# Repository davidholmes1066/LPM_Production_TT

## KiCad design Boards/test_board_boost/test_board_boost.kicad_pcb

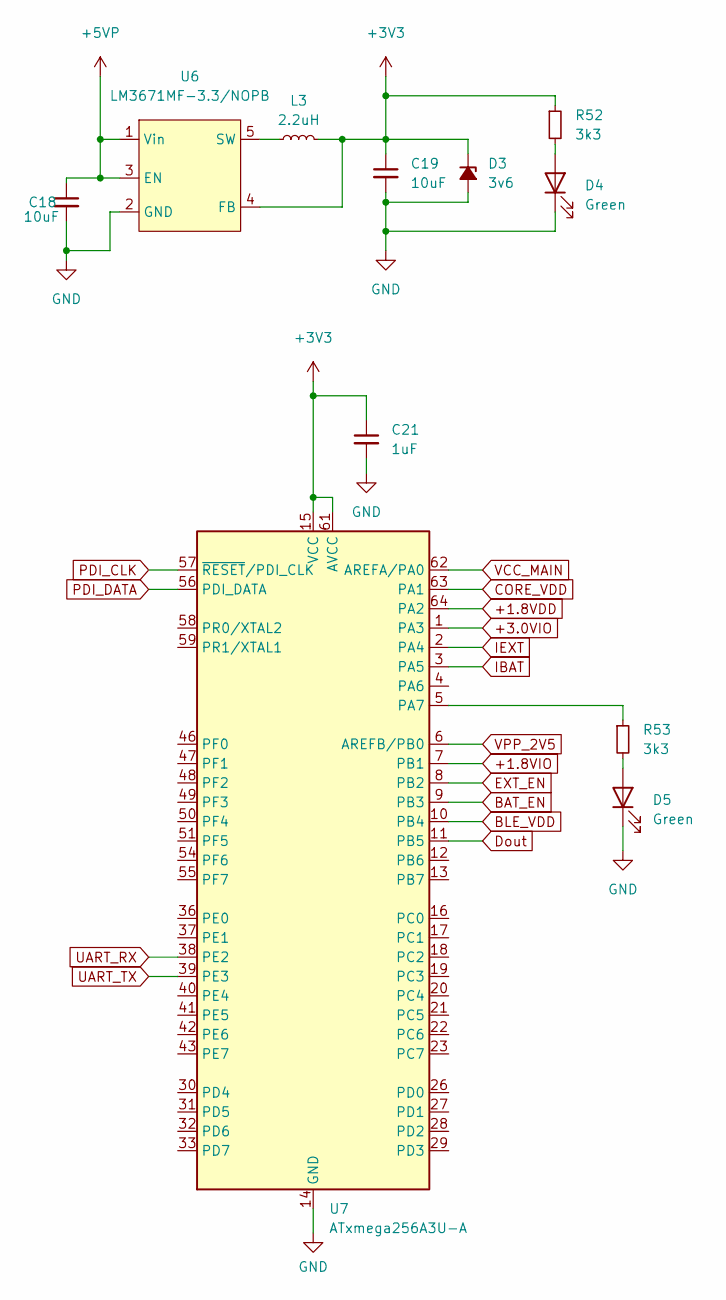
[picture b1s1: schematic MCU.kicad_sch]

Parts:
C18, C19: 10uF; C_0805_2012Metric_Pad1.18x1.45mm_HandSolder
C21: 1uF; C_0805_2012Metric_Pad1.18x1.45mm_HandSolder; Farnell 2346944
D3: 3v6; BZX84C3V6; Farnell 1902466
D4, D5: Green; LED_0402_1005Metric_Pad0.77x0.64mm_HandSolder; Farnell 2507544
L3: 2.2uH; 10uH_boost; Farnell 3865051
R52, R53: 3k3; R_0805_2012Metric_Pad1.20x1.40mm_HandSolder
U6: LM3671MF-3.3/NOPB; SOT-23-5_HandSoldering; Farnell 3008192
U7: ATxmega256A3U-A; TQFP-64_14x14mm_P0.8mm

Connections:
+1.8VDD: U7.64 (PA2); also elsewhere on the board
+1.8VIO: U7.7 (PB1); also elsewhere on the board
+3.0VIO: U7.1 (PA3); also elsewhere on the board
+3V3: C19.1, C21.1, D3.1 (K), L3.2, R52.1, U6.4 (FB), U7.15 (VCC), U7.25 (VCC), U7.35 (VCC), U7.45 (VCC), U7.53 (VCC), U7.61 (AVCC); also elsewhere on the board
+5VP: C18.1, U6.1 (Vin), U6.3 (EN); also elsewhere on the board
BAT_EN: U7.9 (PB3); also elsewhere on the board
BLE_VDD: U7.10 (PB4); also elsewhere on the board
CORE_VDD: U7.63 (PA1); also elsewhere on the board
Dout: U7.11 (PB5); also elsewhere on the board
EXT_EN: U7.8 (PB2); also elsewhere on the board
GND: C18.2, C19.2, C21.2, D3.2 (A), D4.1 (K), D5.1 (K), U6.2 (GND), U7.14 (GND), U7.24 (GND), U7.34 (GND), U7.44 (GND), U7.52 (GND), U7.60 (GND); also elsewhere on the board
IBAT: U7.3 (PA5); also elsewhere on the board
IEXT: U7.2 (PA4); also elsewhere on the board
unnamed: D4.2 (A), R52.2
unnamed: D5.2 (A), R53.2
unnamed: L3.1, U6.5 (SW)
unnamed: R53.1, U7.5 (PA7)
PDI_CLK: U7.57 (~RESET/PDI_CLK); also elsewhere on the board
PDI_DATA: U7.56 (PDI_DATA); also elsewhere on the board
UART_RX: U7.38 (PE2); also elsewhere on the board
UART_TX: U7.39 (PE3); also elsewhere on the board
VCC_MAIN: U7.62 (AREFA/PA0); also elsewhere on the board
VPP_2V5: U7.6 (AREFB/PB0); also elsewhere on the board

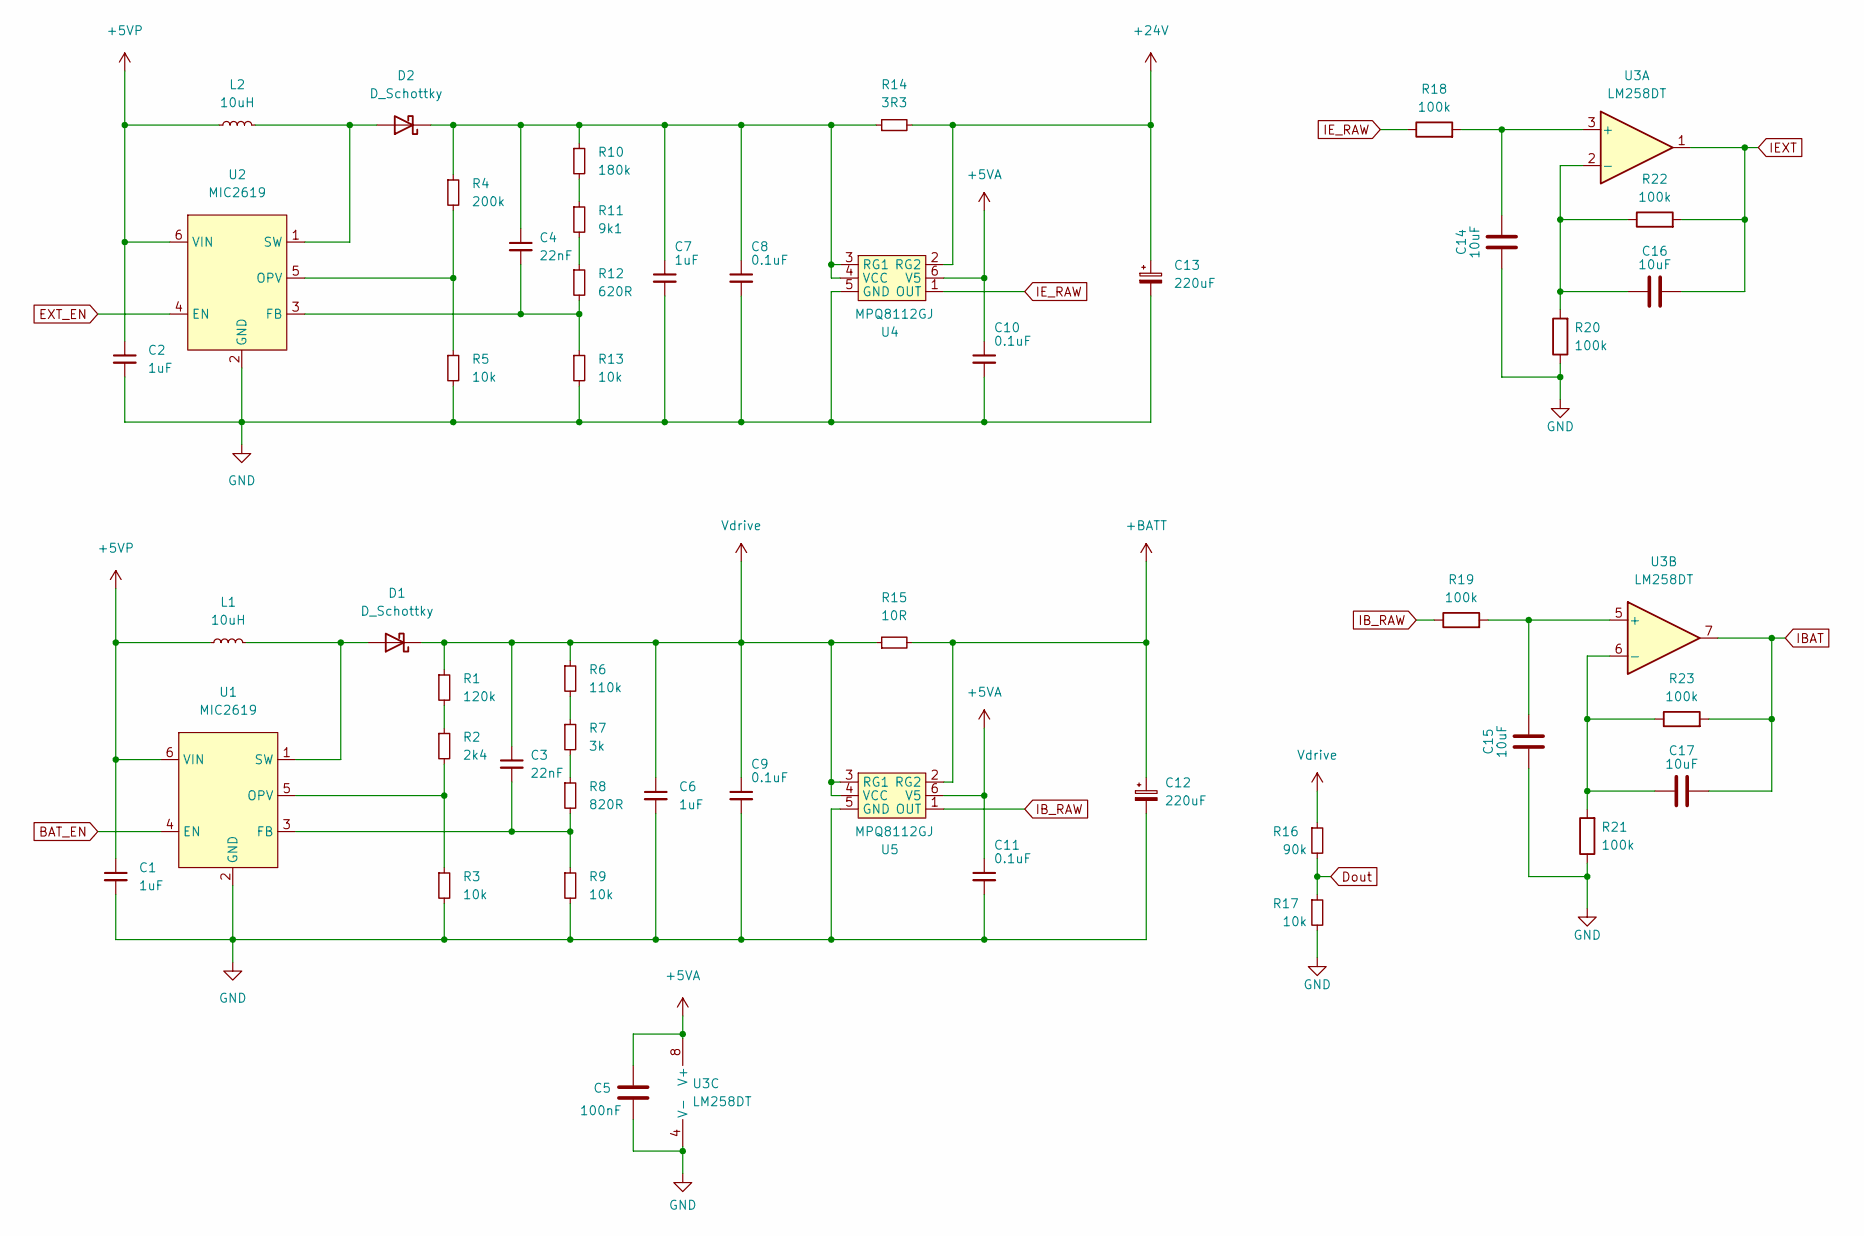
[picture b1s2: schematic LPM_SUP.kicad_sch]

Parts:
C1, C2, C7: 1uF; C_0805_2012Metric_Pad1.18x1.45mm_HandSolder; Farnell 2346944
C3, C4: 22nF; C_0805_2012Metric_Pad1.18x1.45mm_HandSolder
C5: 100nF; C_0805_2012Metric_Pad1.18x1.45mm_HandSolder; FARNELL 2611936
C6: 1uF; C_0805_2012Metric_Pad1.18x1.45mm_HandSolder
C8, C9, C10, C11: 0.1uF; C_0805_2012Metric_Pad1.18x1.45mm_HandSolder
C12, C13: 220uF; CP_Elec_10x10; Farnell 2471976
C14, C15, C16, C17: 10uF; C_0805_2012Metric_Pad1.18x1.45mm_HandSolder; FARNELL 2611936
D1, D2: D_Schottky; D_SOD-323; Farnell 1467544
L1, L2: 10uH; 10uH_boost; Farnell 3865054
R1: 120k; R_0805_2012Metric_Pad1.20x1.40mm_HandSolder
R2: 2k4; R_0805_2012Metric_Pad1.20x1.40mm_HandSolder
R3, R5, R9, R13, R17: 10k; R_0805_2012Metric_Pad1.20x1.40mm_HandSolder
R4: 200k; R_0805_2012Metric_Pad1.20x1.40mm_HandSolder
R6: 110k; R_0805_2012Metric_Pad1.20x1.40mm_HandSolder
R7: 3k; R_0805_2012Metric_Pad1.20x1.40mm_HandSolder
R8: 820R; R_0805_2012Metric_Pad1.20x1.40mm_HandSolder
R10: 180k; R_0805_2012Metric_Pad1.20x1.40mm_HandSolder
R11: 9k1; R_0805_2012Metric_Pad1.20x1.40mm_HandSolder
R12: 620R; R_0805_2012Metric_Pad1.20x1.40mm_HandSolder
R14: 3R3; R_0805_2012Metric_Pad1.20x1.40mm_HandSolder
R15: 10R; R_0805_2012Metric_Pad1.20x1.40mm_HandSolder
R16: 90k; R_0805_2012Metric_Pad1.20x1.40mm_HandSolder
R18, R19, R20, R21, R22, R23: 100k; R_0805_2012Metric_Pad1.20x1.40mm_HandSolder
U1, U2: MIC2619; MIC2619YD6-TR; Farnell 2509963
U3: LM258DT; SO-8_5.3x6.2mm_P1.27mm; Farnell 2382607
U4, U5: MPQ8112GJ; SOT-23-6_Handsoldering; Farnell 3922485

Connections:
+5VP: C1.1, C2.1, C5.1, C10.1, C11.1, L1.1, L2.1, U1.6 (VIN), U2.6 (VIN), U3.8 (V+), U4.6 (V5), U5.6 (V5); also elsewhere on the board
+24V: C13.1, R14.2, U4.2 (RG2); also elsewhere on the board
+BATT: C12.1, R15.2, U5.2 (RG2); also elsewhere on the board
BAT_EN: U1.4 (EN); also elsewhere on the board
Dout: R16.2, R17.1; also elsewhere on the board
EXT_EN: U2.4 (EN); also elsewhere on the board
GND: C1.2, C2.2, C5.2, C6.2, C7.2, C8.2, C9.2, C10.2, C11.2, C12.2, C13.2, C14.1, C15.1, R3.2, R5.2, R9.2, R13.2, R17.2, R20.1, R21.1, U1.2 (GND), U2.2 (GND), U3.4 (V-), U4.5 (GND), U5.5 (GND); also elsewhere on the board
IBAT: C17.2, R23.2, U3.7; also elsewhere on the board
IB_RAW: R19.1, U5.1 (OUT)
IEXT: C16.2, R22.2, U3.1; also elsewhere on the board
IE_RAW: R18.1, U4.1 (OUT)
unnamed: C3.2, R8.2, R9.1, U1.3 (FB)
unnamed: C4.1, C7.1, C8.1, D2.1 (K), R4.1, R10.1, R14.1, U4.3 (RG1), U4.4 (VCC)
unnamed: C4.2, R12.2, R13.1, U2.3 (FB)
unnamed: C14.2, R18.2, U3.3 (+)
unnamed: C15.2, R19.2, U3.5 (+)
unnamed: C16.1, R20.2, R22.1, U3.2 (-)
unnamed: C17.1, R21.2, R23.1, U3.6 (-)
unnamed: D1.2 (A), L1.2, U1.1 (SW)
unnamed: D2.2 (A), L2.2, U2.1 (SW)
unnamed: R1.2, R2.1
unnamed: R2.2, R3.1, U1.5 (OPV)
unnamed: R4.2, R5.1, U2.5 (OPV)
unnamed: R6.2, R7.1
unnamed: R7.2, R8.1
unnamed: R10.2, R11.1
unnamed: R11.2, R12.1
Vdrive: C3.1, C6.1, C9.1, D1.1 (K), R1.1, R6.1, R15.1, R16.1, U5.3 (RG1), U5.4 (VCC)

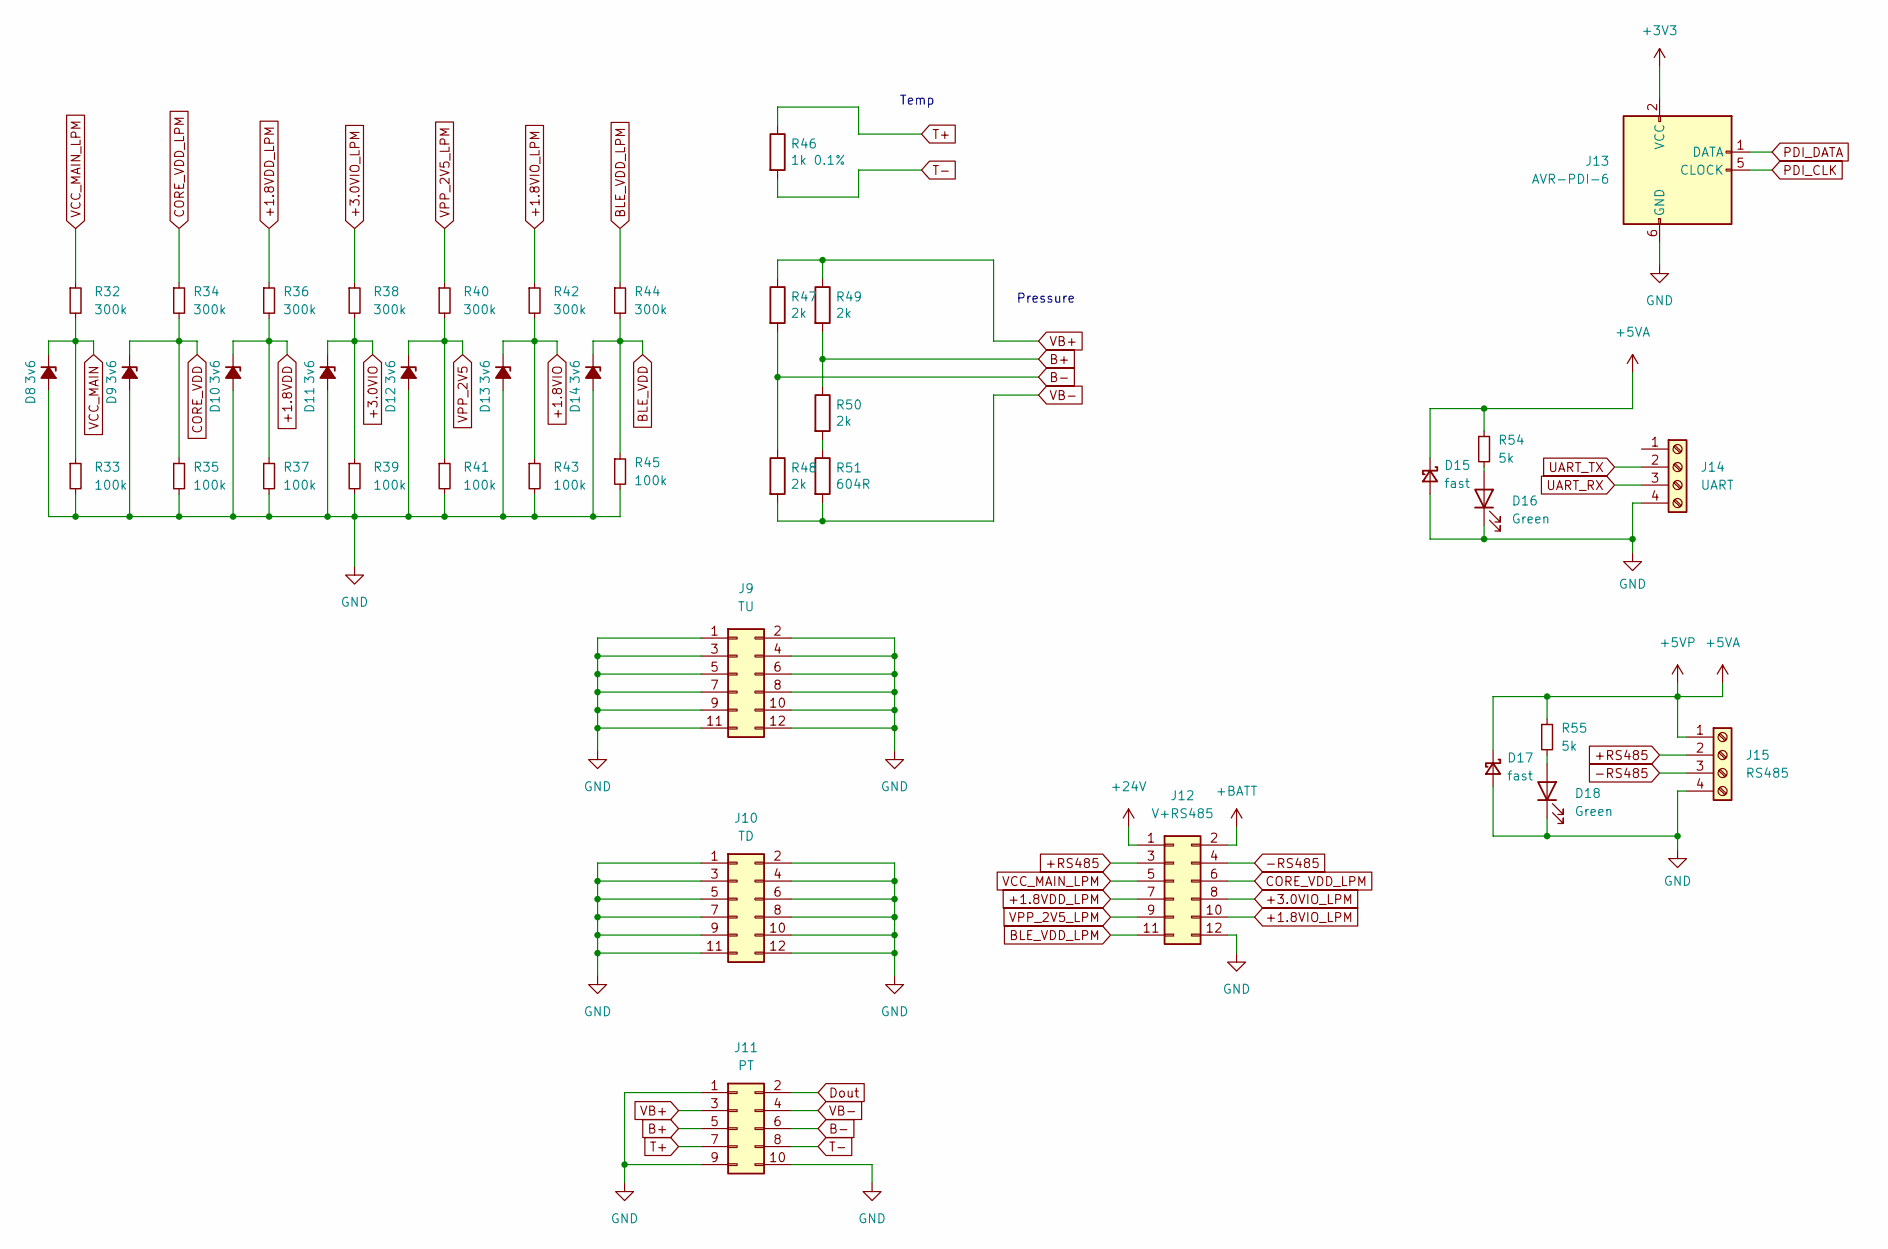
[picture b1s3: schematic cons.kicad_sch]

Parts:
D8, D9, D10, D11, D12, D13, D14: 3v6; BZX84C3V6; Farnell 1902466
D15, D17: fast; D_SOD-128; Farnell 1829204
D16, D18: Green; LED_0402_1005Metric_Pad0.77x0.64mm_HandSolder; Farnell 2507544
J9: TU; PinHeader_2x06_P2.54mm_Vertical
J10: TD; PinHeader_2x06_P2.54mm_Vertical
J11: PT; PinHeader_2x05_P2.54mm_Vertical
J12: V+RS485; PinHeader_2x06_P2.54mm_Vertical
J13: AVR-PDI-6; AVR-PDI-TAG-CONNECT
J14: UART; 4pos_terminal; Farnell 2007987
J15: RS485; 4pos_terminal; Farnell 2007987
R32, R34, R36, R38, R40, R42, R44: 300k; R_0805_2012Metric_Pad1.20x1.40mm_HandSolder
R33, R35, R37, R39, R41, R43, R45: 100k; R_0805_2012Metric_Pad1.20x1.40mm_HandSolder
R46: 1k 0.1%; R_0805_2012Metric_Pad1.20x1.40mm_HandSolder
R47, R48, R49, R50: 2k; R_0805_2012Metric_Pad1.20x1.40mm_HandSolder
R51: 604R; R_0805_2012Metric_Pad1.20x1.40mm_HandSolder
R54, R55: 5k; R_0805_2012Metric_Pad1.20x1.40mm_HandSolder

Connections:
+1.8VDD: D10.1 (K), R36.2, R37.1; also elsewhere on the board
+1.8VDD_LPM: J12.7, R36.1
+1.8VIO: D13.1 (K), R42.2, R43.1; also elsewhere on the board
+1.8VIO_LPM: J12.10, R42.1
+3.0VIO: D11.1 (K), R38.2, R39.1; also elsewhere on the board
+3.0VIO_LPM: J12.8, R38.1
+3V3: J13.2 (VCC); also elsewhere on the board
+5VP: D15.1 (K), D17.1 (K), J15.1, R54.1, R55.1; also elsewhere on the board
+24V: J12.1; also elsewhere on the board
+BATT: J12.2; also elsewhere on the board
+RS485: J12.3, J15.2
-RS485: J12.4, J15.3
B+: J11.5, R49.2, R50.1
B-: J11.6, R47.2, R48.1
BLE_VDD: D14.1 (K), R44.2, R45.1; also elsewhere on the board
BLE_VDD_LPM: J12.11, R44.1
CORE_VDD: D9.1 (K), R34.2, R35.1; also elsewhere on the board
CORE_VDD_LPM: J12.6, R34.1
Dout: J11.2; also elsewhere on the board
GND: D8.2 (A), D9.2 (A), D10.2 (A), D11.2 (A), D12.2 (A), D13.2 (A), D14.2 (A), D15.2 (A), D16.1 (K), D17.2 (A), D18.1 (K), J9.1, J9.2, J9.3, J9.4, J9.5, J9.6, J9.7, J9.8, J9.9, J9.10, J9.11, J9.12, J10.1, J10.2, J10.3, J10.4, J10.5, J10.6, J10.7, J10.8, J10.9, J10.10, J10.11, J10.12, J11.1, J11.9, J11.10, J12.12, J13.6 (GND), J14.4, J15.4, R33.2, R35.2, R37.2, R39.2, R41.2, R43.2, R45.2; also elsewhere on the board
unnamed: D16.2 (A), R54.2
unnamed: D18.2 (A), R55.2
unnamed: R50.2, R51.1
PDI_CLK: J13.5 (CLOCK); also elsewhere on the board
PDI_DATA: J13.1 (DATA); also elsewhere on the board
T+: J11.7, R46.1
T-: J11.8, R46.2
UART_RX: J14.3; also elsewhere on the board
UART_TX: J14.2; also elsewhere on the board
VB+: J11.3, R47.1, R49.1
VB-: J11.4, R48.2, R51.2
VCC_MAIN: D8.1 (K), R32.2, R33.1; also elsewhere on the board
VCC_MAIN_LPM: J12.5, R32.1
VPP_2V5: D12.1 (K), R40.2, R41.1; also elsewhere on the board
VPP_2V5_LPM: J12.9, R40.1

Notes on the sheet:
Pressure
Temp

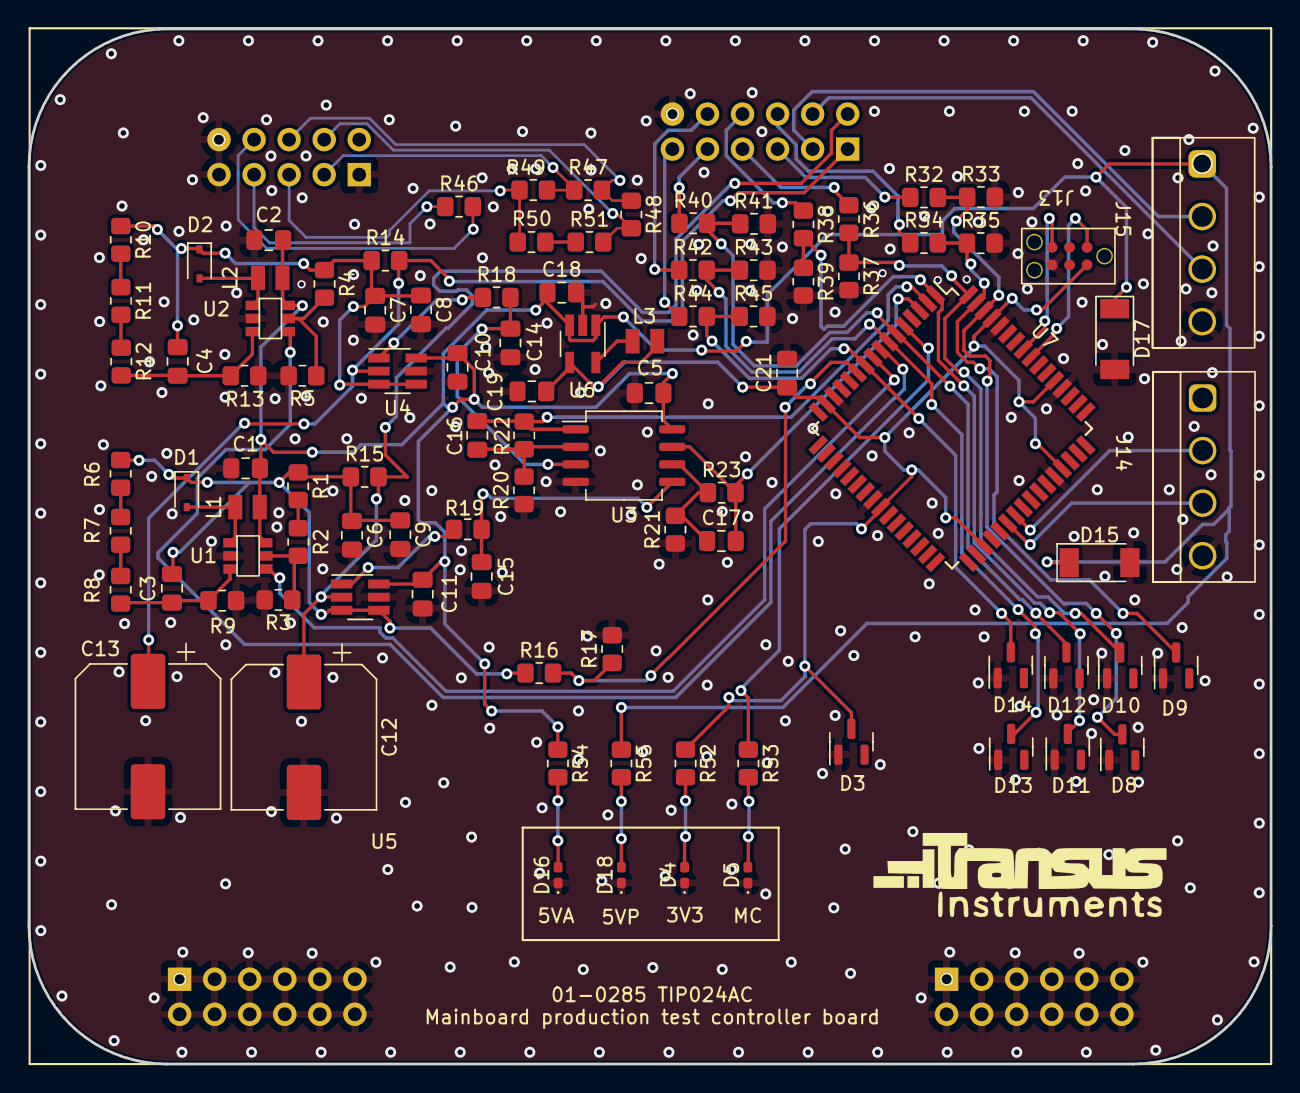
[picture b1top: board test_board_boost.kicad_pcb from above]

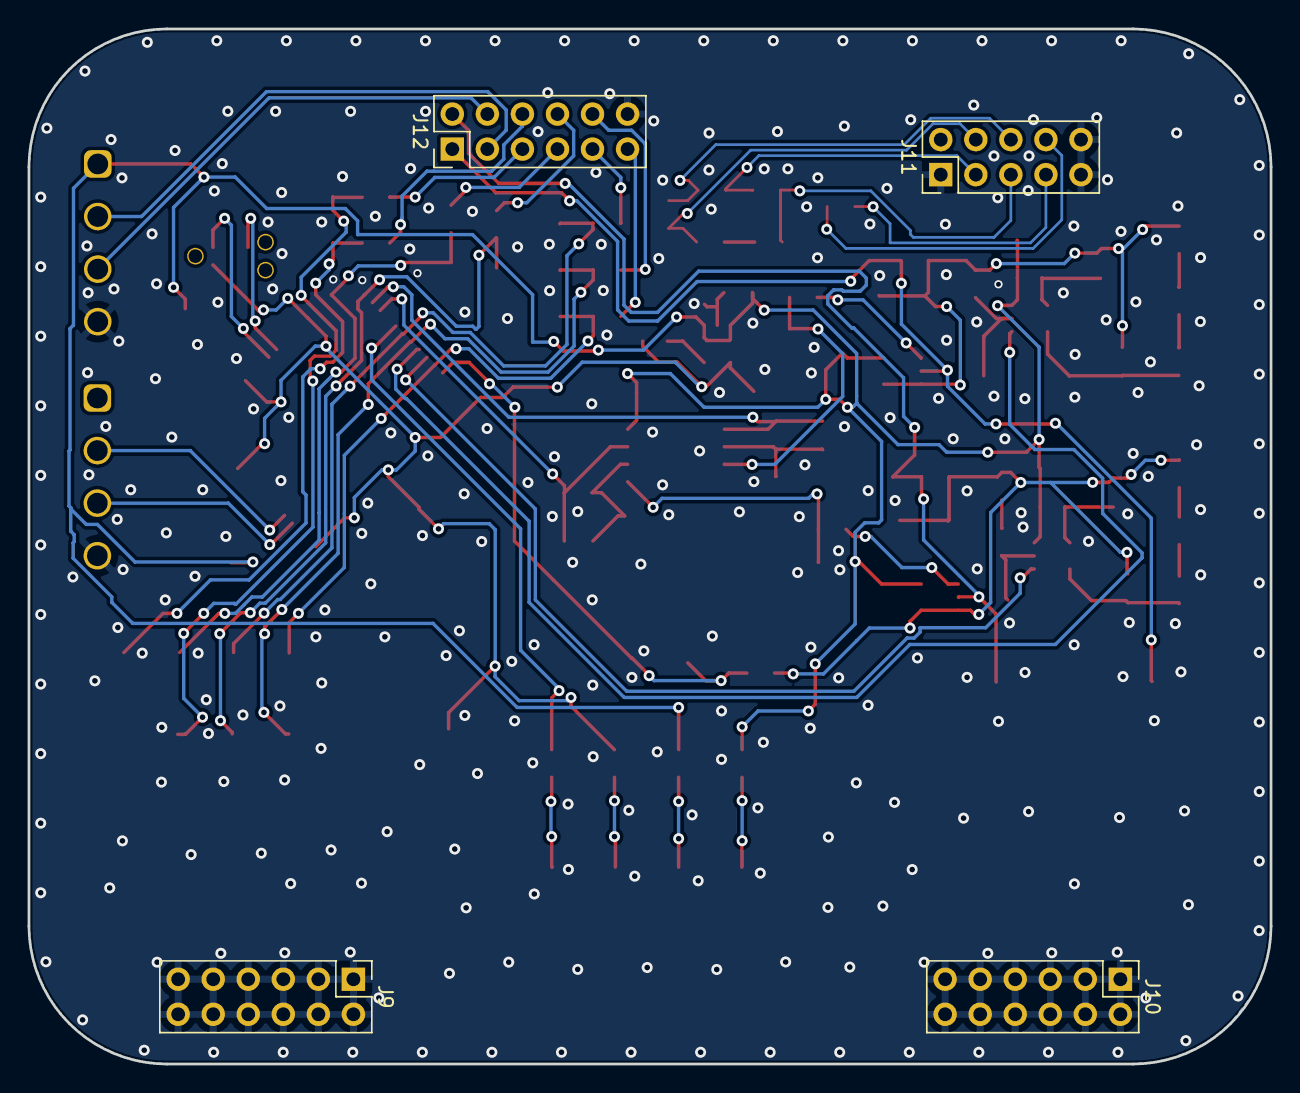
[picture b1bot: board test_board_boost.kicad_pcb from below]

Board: 4 copper layers, 90.0 x 75.0 mm, 100 parts (4 on the bottom side), 62 nets.

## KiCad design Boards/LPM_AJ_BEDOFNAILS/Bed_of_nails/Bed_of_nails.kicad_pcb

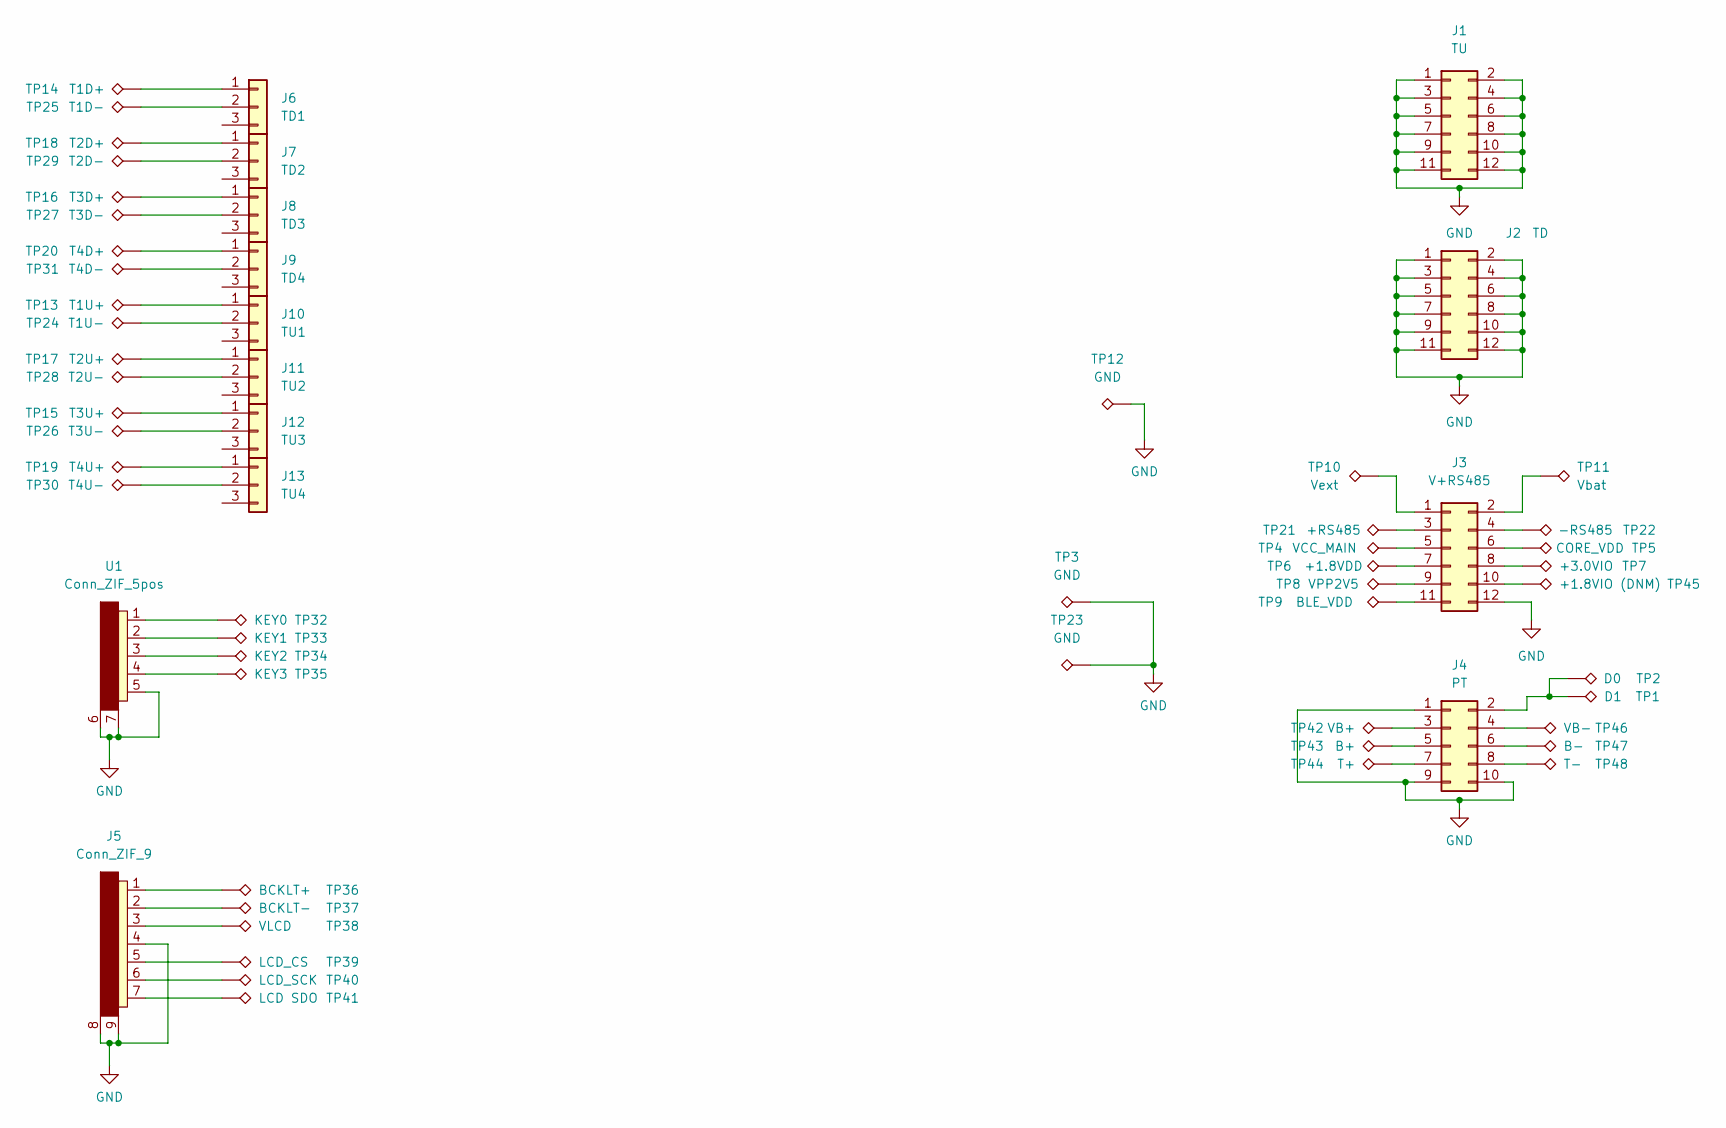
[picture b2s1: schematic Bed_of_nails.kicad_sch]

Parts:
J1: TU; PinHeader_2x06_P2.54mm_Vertical; Farnell 2827902
J2: TD; PinHeader_2x06_P2.54mm_Vertical; Farnell 2827902
J3: V+RS485; PinHeader_2x06_P2.54mm_Vertical; Farnell 2827902
J4: PT; PinHeader_2x05_P2.54mm_Vertical; Farnell 1593490
J5: Conn_ZIF_9; Conn_ZIF_7pos; Farnell 3215773
J6: TD1; Molex_55487-0319_LPMTRANS
J7: TD2; Molex_55487-0319_LPMTRANS
J8: TD3; Molex_55487-0319_LPMTRANS
J9: TD4; Molex_55487-0319_LPMTRANS
J10: TU1; Molex_55487-0319_LPMTRANS
J11: TU2; Molex_55487-0319_LPMTRANS
J12: TU3; Molex_55487-0319_LPMTRANS
J13: TU4; Molex_55487-0319_LPMTRANS
TP1: D1; INGUN_KS-075-47-G-10_KS-07547G10
TP2: D0; INGUN_KS-075-47-G-10_KS-07547G10
TP3, TP12, TP23: GND; INGUN_KS-075-47-G-10_KS-07547G10
TP4: VCC_MAIN; INGUN_KS-075-47-G-10_KS-07547G10
TP5: CORE_VDD; INGUN_KS-075-47-G-10_KS-07547G10
TP6: +1.8VDD; INGUN_KS-075-47-G-10_KS-07547G10
TP7: +3.0VIO; INGUN_KS-075-47-G-10_KS-07547G10
TP8: VPP2V5; INGUN_KS-075-47-G-10_KS-07547G10
TP9: BLE_VDD; INGUN_KS-075-47-G-10_KS-07547G10
TP10: Vext; INGUN_KS-075-47-G-10_KS-07547G10
TP11: Vbat; INGUN_KS-075-47-G-10_KS-07547G10
TP13: T1U+; INGUN_KS-075-47-G-10_KS-07547G10
TP14: T1D+; INGUN_KS-075-47-G-10_KS-07547G10
TP15: T3U+; INGUN_KS-075-47-G-10_KS-07547G10
TP16: T3D+; INGUN_KS-075-47-G-10_KS-07547G10
TP17: T2U+; INGUN_KS-075-47-G-10_KS-07547G10
TP18: T2D+; INGUN_KS-075-47-G-10_KS-07547G10
TP19: T4U+; INGUN_KS-075-47-G-10_KS-07547G10
TP20: T4D+; INGUN_KS-075-47-G-10_KS-07547G10
TP21: +RS485; INGUN_KS-075-47-G-10_KS-07547G10
TP22: -RS485; INGUN_KS-075-47-G-10_KS-07547G10
TP24: T1U-; INGUN_KS-075-47-G-10_KS-07547G10
TP25: T1D-; INGUN_KS-075-47-G-10_KS-07547G10
TP26: T3U-; INGUN_KS-075-47-G-10_KS-07547G10
TP27: T3D-; INGUN_KS-075-47-G-10_KS-07547G10
TP28: T2U-; INGUN_KS-075-47-G-10_KS-07547G10
TP29: T2D-; INGUN_KS-075-47-G-10_KS-07547G10
TP30: T4U-; INGUN_KS-075-47-G-10_KS-07547G10
TP31: T4D-; INGUN_KS-075-47-G-10_KS-07547G10
TP32: KEY0; INGUN_KS-075-47-G-10_KS-07547G10
TP33: KEY1; INGUN_KS-075-47-G-10_KS-07547G10
TP34: KEY2; INGUN_KS-075-47-G-10_KS-07547G10
TP35: KEY3; INGUN_KS-075-47-G-10_KS-07547G10
TP36: BCKLT+; INGUN_KS-075-47-G-10_KS-07547G10
TP37: BCKLT-; INGUN_KS-075-47-G-10_KS-07547G10
TP38: VLCD; INGUN_KS-075-47-G-10_KS-07547G10
TP39: LCD_CS; INGUN_KS-075-47-G-10_KS-07547G10
TP40: LCD_SCK; INGUN_KS-075-47-G-10_KS-07547G10
TP41: LCD SDO; INGUN_KS-075-47-G-10_KS-07547G10
TP42: VB+; INGUN_KS-075-47-G-10_KS-07547G10
TP43: B+; INGUN_KS-075-47-G-10_KS-07547G10
TP44: T+; INGUN_KS-075-47-G-10_KS-07547G10
TP45: +1.8VIO (DNM); INGUN_KS-075-47-G-10_KS-07547G10
TP46: VB-; INGUN_KS-075-47-G-10_KS-07547G10
TP47: B-; INGUN_KS-075-47-G-10_KS-07547G10
TP48: T-; INGUN_KS-075-47-G-10_KS-07547G10
U1: Conn_ZIF_5pos; Farnell 3215771

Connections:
GND: J1.1, J1.2, J1.3, J1.4, J1.5, J1.6, J1.7, J1.8, J1.9, J1.10, J1.11, J1.12, J2.1, J2.2, J2.3, J2.4, J2.5, J2.6, J2.7, J2.8, J2.9, J2.10, J2.11, J2.12, J3.12, J4.1, J4.9, J4.10, J5.4, J5.8, J5.9, TP3.1, TP12.1, TP23.1, U1.5, U1.6, U1.7
unnamed: J3.1, TP10.1
unnamed: J3.2, TP11.1
unnamed: J3.3, TP21.1
unnamed: J3.4, TP22.1
unnamed: J3.5, TP4.1
unnamed: J3.6, TP5.1
unnamed: J3.7, TP6.1
unnamed: J3.8, TP7.1
unnamed: J3.9, TP8.1
unnamed: J3.10, TP45.1
unnamed: J3.11, TP9.1
unnamed: J4.2, TP1.1, TP2.1
unnamed: J4.3, TP42.1
unnamed: J4.4, TP46.1
unnamed: J4.5, TP43.1
unnamed: J4.6, TP47.1
unnamed: J4.7, TP44.1
unnamed: J4.8, TP48.1
unnamed: J5.1, TP36.1
unnamed: J5.2, TP37.1
unnamed: J5.3, TP38.1
unnamed: J5.5, TP39.1
unnamed: J5.6, TP40.1
unnamed: J5.7, TP41.1
unnamed: J6.1, TP14.1
unnamed: J6.2, TP25.1
unnamed: J7.1, TP18.1
unnamed: J7.2, TP29.1
unnamed: J8.1, TP16.1
unnamed: J8.2, TP27.1
unnamed: J9.1, TP20.1
unnamed: J9.2, TP31.1
unnamed: J10.1, TP13.1
unnamed: J10.2, TP24.1
unnamed: J11.1, TP17.1
unnamed: J11.2, TP28.1
unnamed: J12.1, TP15.1
unnamed: J12.2, TP26.1
unnamed: J13.1, TP19.1
unnamed: J13.2, TP30.1
unnamed: TP32.1, U1.1
unnamed: TP33.1, U1.2
unnamed: TP34.1, U1.3
unnamed: TP35.1, U1.4

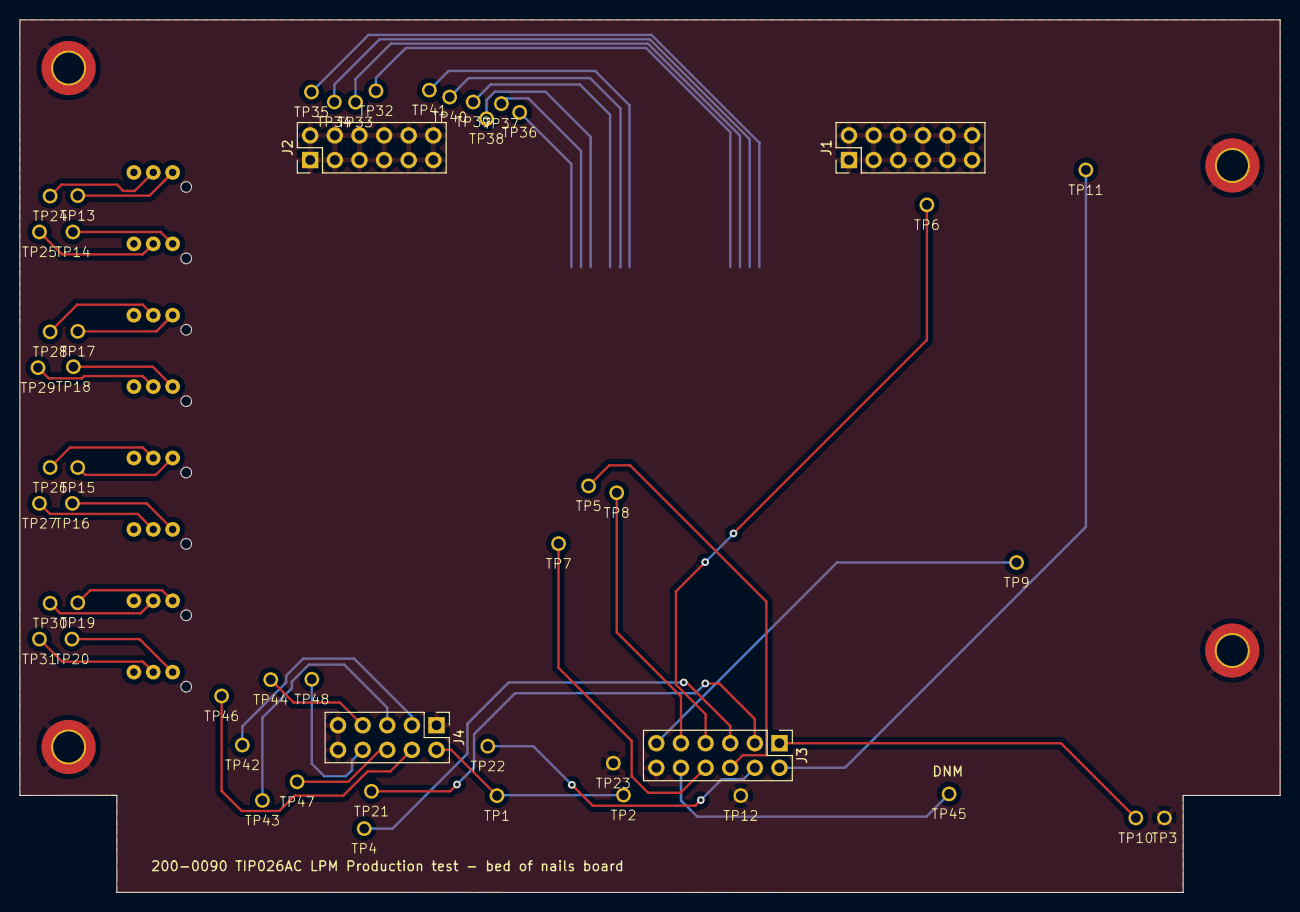
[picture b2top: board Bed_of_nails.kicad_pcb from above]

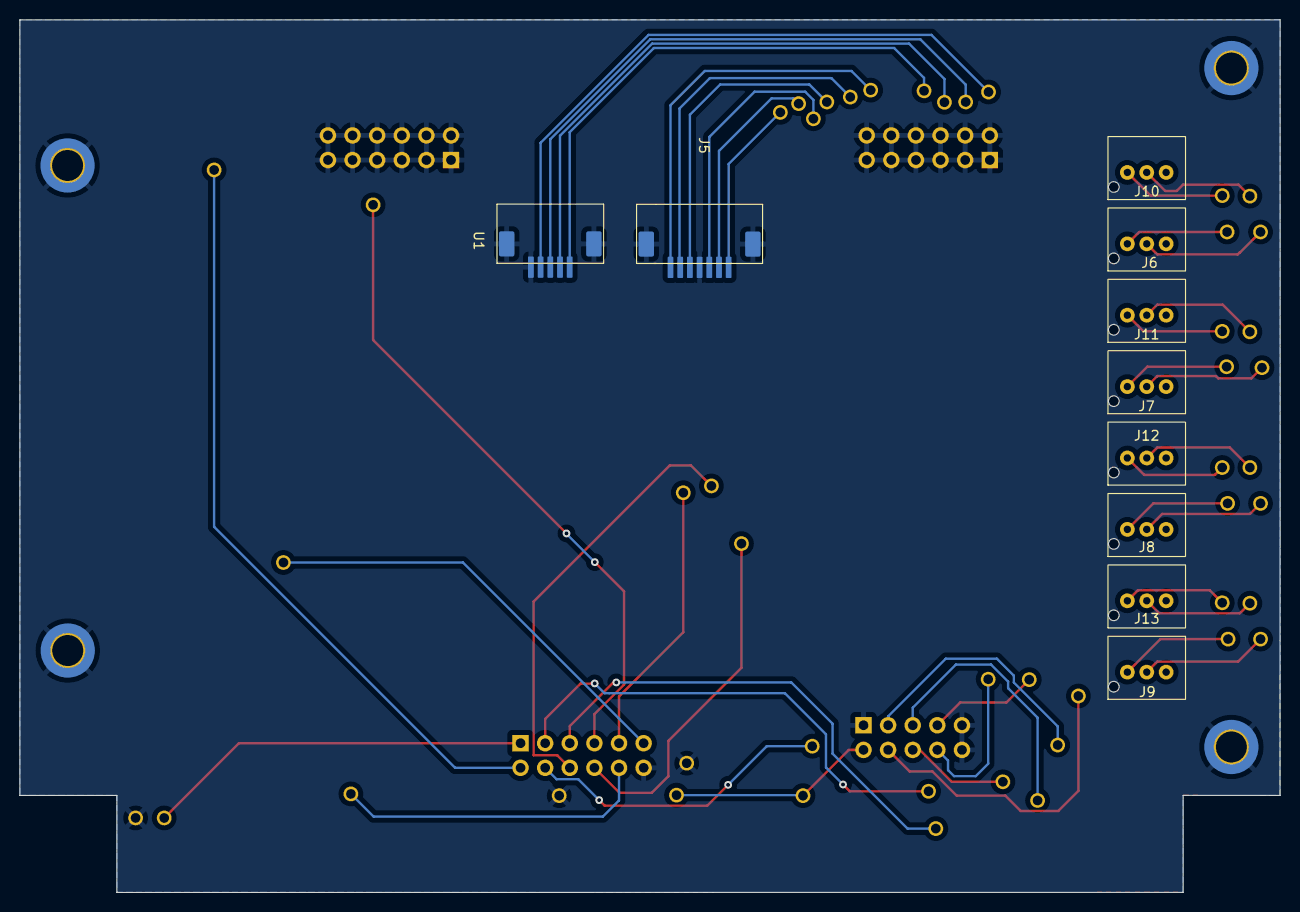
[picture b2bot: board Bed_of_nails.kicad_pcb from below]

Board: 2 copper layers, 130.0 x 90.0 mm, 62 parts (10 on the bottom side), 45 nets.
